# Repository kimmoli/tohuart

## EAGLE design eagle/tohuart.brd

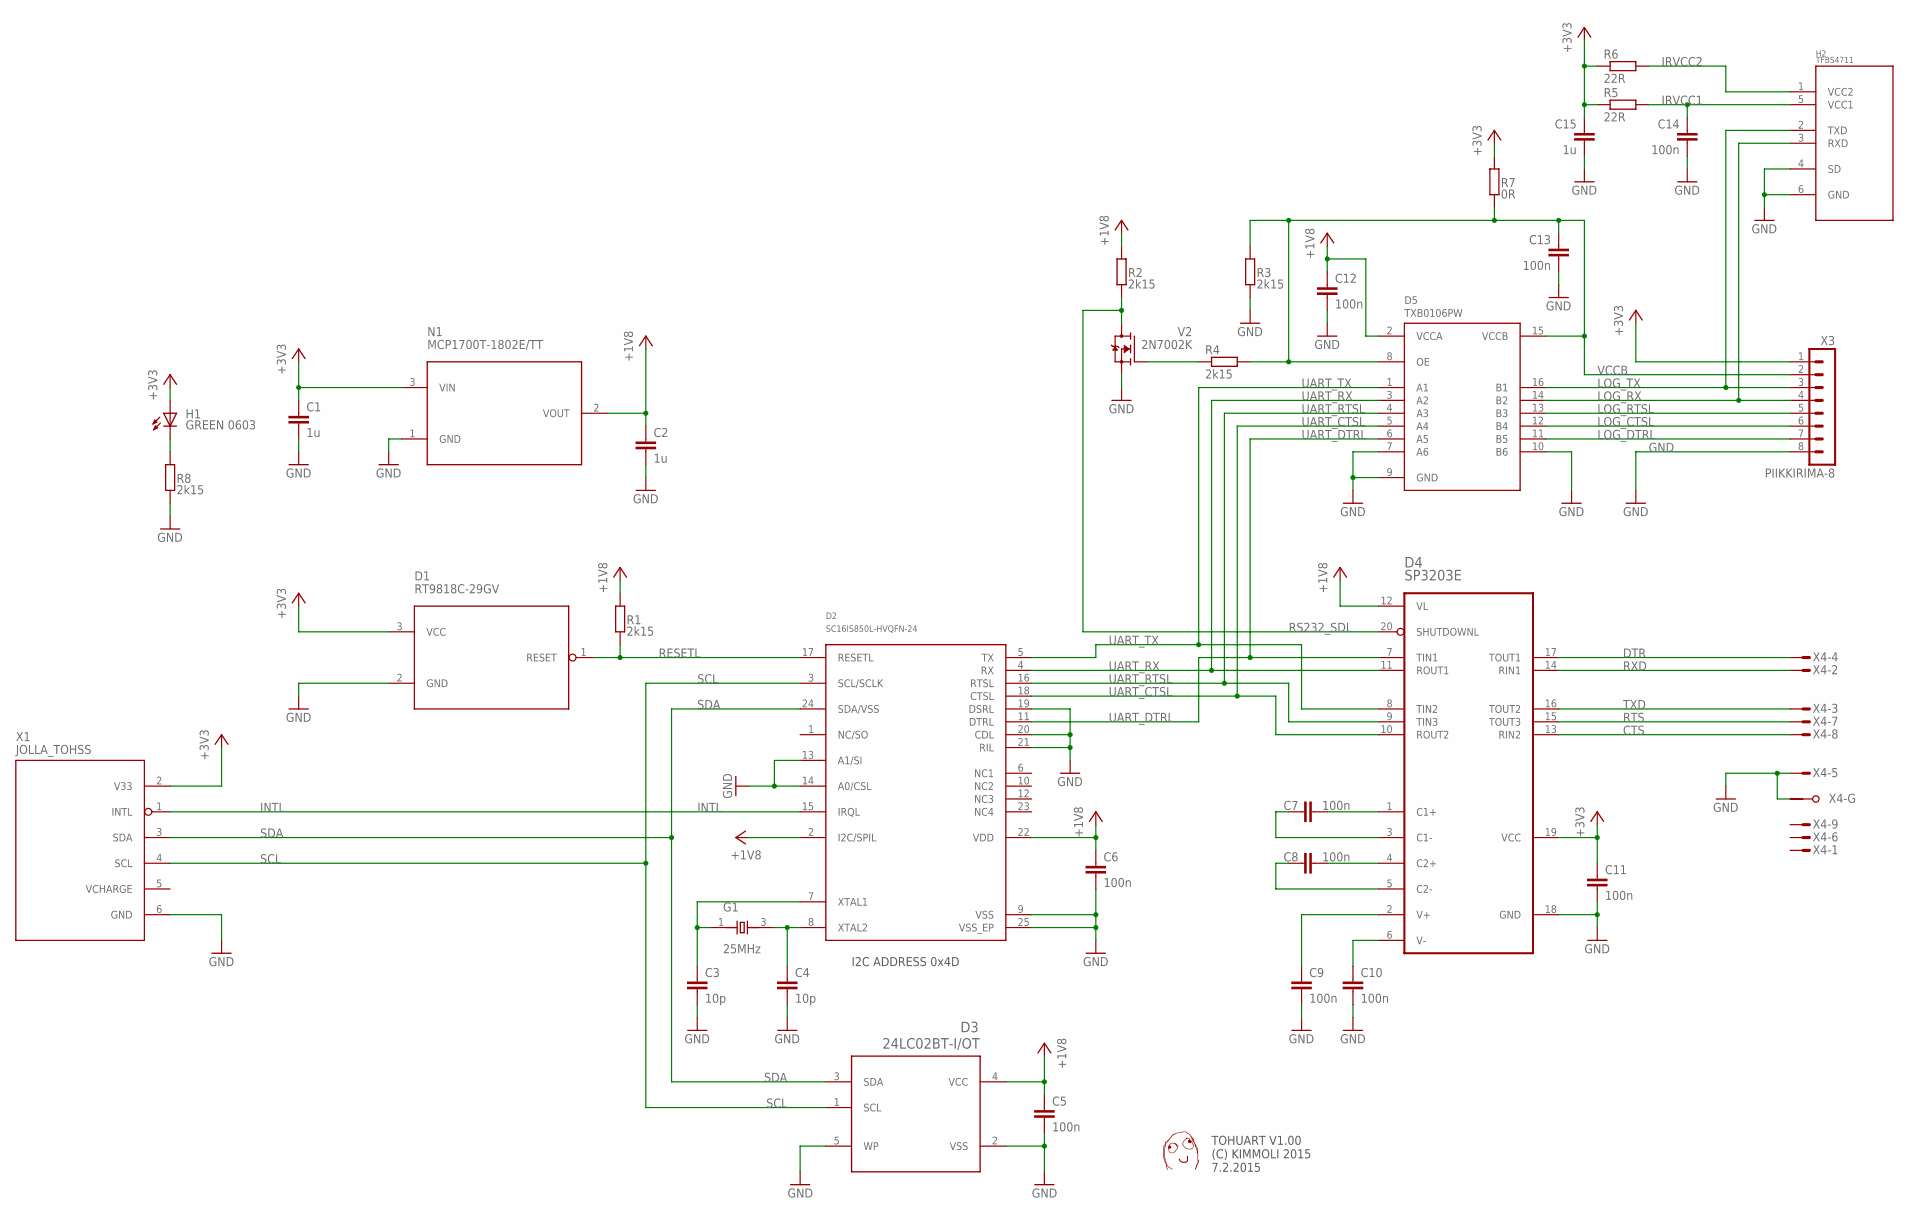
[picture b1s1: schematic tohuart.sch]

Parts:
C1, C2, C15: 1u; C0603
C3, C4: 10p; C0603
C5, C6, C7, C8, C9, C10, C11, C12, C13, C14: 100n; C0603
D1: RT9818C-29GV; SOT23
D2: SC16IS850L-HVQFN-24; HVQFN-24
D3: 24LC02BT-I/OT; SOT95P280X145-5N
D4: SP3203E; TSSOP-20
D5: TXB0106PW; TSSOP-16-065
G1: 25MHz; X_3225
H1: GREEN 0603; CHIP-LED0603
H2: TFBS4711
N1: MCP1700T-1802E/TT; SOT23
R1, R2, R3, R4, R8: 2k15; R0603
R5, R6: 22R; R0603
R7: 0R; R0603
U$1: DAFUG
V2: 2N7002K; SOT23
X1: JOLLA_TOHSS; JOLLA_TOH_POGOPADS
X3: PIIKKIRIMA-8
X4: M09VPS; M09VP

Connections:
+1V8: C2.1, C5.1, C6.1, C12.1, D2.2 (I2C/SPIL), D2.22 (VDD), D3.4 (VCC), D4.12 (VL), D5.2 (VCCA), N1.2 (VOUT), R1.2, R2.2
+3V3: C1.1, C11.1, C15.1, D1.3 (VCC), D4.19 (VCC), H1.A, N1.3 (VIN), R5.1, R6.1, R7.2, X1.2 (V33), X3.1
CTS: D4.13 (RIN2), X4.8 (M)
DTR: D4.17 (TOUT1), X4.4 (M)
GND: C1.2, C2.2, C3.2, C4.2, C5.2, C6.2, C9.2, C10.2, C11.2, C12.2, C13.2, C14.2, C15.2, D1.2 (GND), D2.9 (VSS), D2.13 (A1/SI), D2.14 (A0/CSL), D2.19 (DSRL), D2.20 (CDL), D2.21 (RIL), D2.25 (VSS_EP), D3.2 (VSS), D3.5 (WP), D4.18 (GND), D5.7 (A6), D5.9 (GND), D5.10 (B6), H2.4 (SD), H2.6 (GND), N1.1 (GND), R3.1, R8.1, V2.2 (S), X1.6 (GND), X3.8, X4.5 (M), X4.G1
INTL: D2.15 (IRQL), X1.1 (INTL)
IRVCC1: C14.1, H2.5 (VCC1), R5.2
IRVCC2: H2.1 (VCC2), R6.2
LOG_CTSL: D5.12 (B4), X3.6
LOG_DTRL: D5.11 (B5), X3.7
LOG_RTSL: D5.13 (B3), X3.5
LOG_RX: D5.14 (B2), H2.3 (RXD), X3.4
LOG_TX: D5.16 (B1), H2.2 (TXD), X3.3
unnamed: R4.1, V2.1 (G)
unnamed: H1.C, R8.2
unnamed: C10.1, D4.6 (V-)
unnamed: C9.1, D4.2 (V+)
unnamed: C8.1, D4.5 (C2-)
unnamed: C8.2, D4.4 (C2+)
unnamed: C7.1, D4.3 (C1-)
unnamed: C7.2, D4.1 (C1+)
unnamed: C4.1, D2.8 (XTAL2), G1.3 (X2)
unnamed: C3.1, D2.7 (XTAL1), G1.1 (X1)
RESETL: D1.1 (RESET), D2.17 (RESETL), R1.1
RS232_SDL: D4.20 (SHUTDOWNL), R2.1, V2.3 (D)
RTS: D4.15 (TOUT3), X4.7 (M)
RXD: D4.14 (RIN1), X4.2 (M)
SCL: D2.3 (SCL/SCLK), D3.1 (SCL), X1.4 (SCL)
SDA: D2.24 (SDA/VSS), D3.3 (SDA), X1.3 (SDA)
TXD: D4.16 (TOUT2), X4.3 (M)
UART_CTSL: D2.18 (CTSL), D4.10 (ROUT2), D5.5 (A4)
UART_DTRL: D2.11 (DTRL), D4.7 (TIN1), D5.6 (A5)
UART_RTSL: D2.16 (RTSL), D4.9 (TIN3), D5.4 (A3)
UART_RX: D2.4 (RX), D4.11 (ROUT1), D5.3 (A2)
UART_TX: D2.5 (TX), D4.8 (TIN2), D5.1 (A1)
VCCB: C13.1, D5.8 (OE), D5.15 (VCCB), R3.2, R4.2, R7.1, X3.2

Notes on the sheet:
I2C ADDRESS 0x4D
TOHUART V1.00 (C) KIMMOLI 2015 7.2.2015

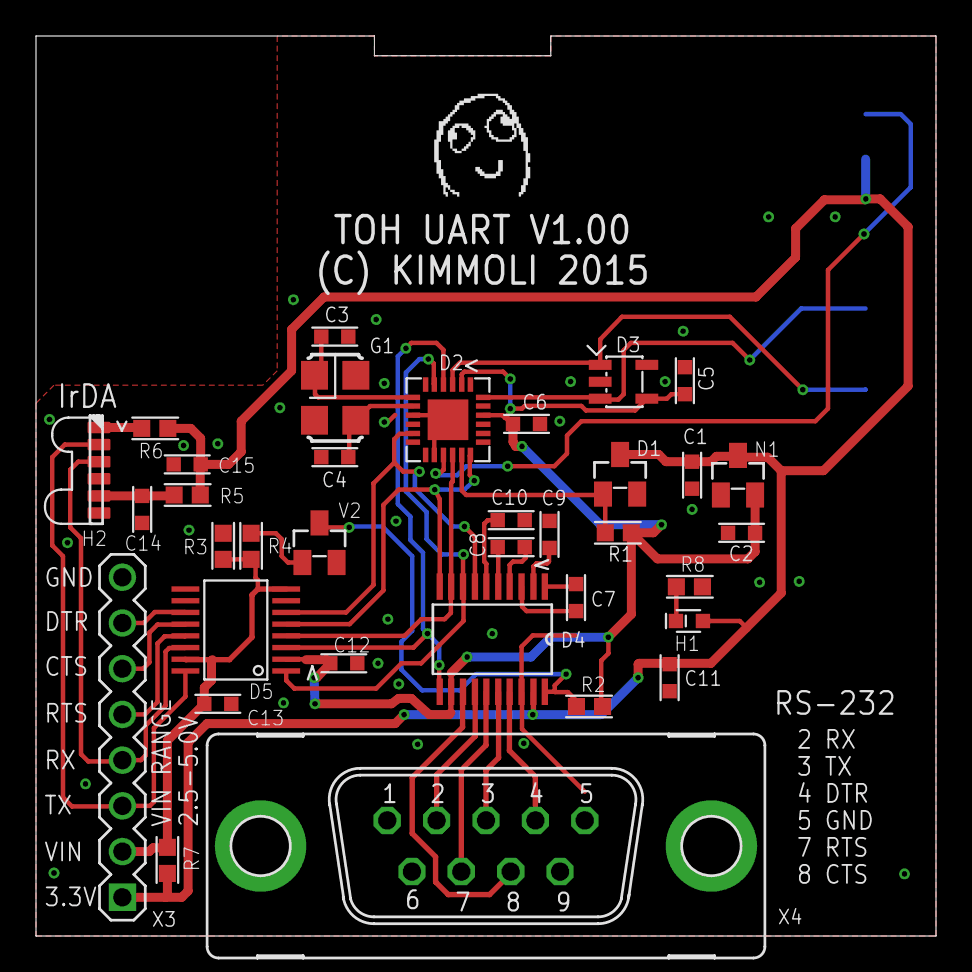
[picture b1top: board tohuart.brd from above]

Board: 2 copper layers, 50.0 x 50.0 mm, 37 parts (0 on the bottom side), 36 nets.

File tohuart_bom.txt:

Qty Value               Device              Package            Parts                                       Description                
1                       M09VPS              M09VP              X4                                          SUB-D                      
1   0R                  R-EU_R0603          R0603              R7                                          RESISTOR, European symbol  
10  100n                C-EUC0603           C0603              C5, C6, C7, C8, C9, C10, C11, C12, C13, C14 CAPACITOR, European symbol 
2   10p                 C-EUC0603           C0603              C3, C4                                      CAPACITOR, European symbol 
3   1u                  C-EUC0603           C0603              C1, C2, C15                                 CAPACITOR, European symbol 
2   22R                 R-EU_R0603          R0603              R5, R6                                      RESISTOR, European symbol  
1   24LC02BT-I/OT       24LC02BT-I/OT       SOT95P280X145-5N   D3                                          Serial EEPROM              
1   25MHz               XTAL_3225_SMD       X_3225             G1                                          CRYSTAL CLOCK OSCILLATORS  
1   2N7002K             2N7002K             SOT23              V2                                                                     
5   2k15                R-EU_R0603          R0603              R1, R2, R3, R4, R8                          RESISTOR, European symbol  
1   GREEN 0603          LEDCHIP-LED0603     CHIP-LED0603       H1                                          LED                        
1   MCP1700T-1802E/TT   MCP1700T-1802E/TT   SOT23              N1                                                                     
1   PIIKKIRIMA-8        PIIKKIRIMA-8        PIIKKIRIMA-8       X3                                                                     
1   RT9818C-29GV        RT9818C-29GV        SOT23              D1                                                                     
1   SC16IS850L-HVQFN-24 SC16IS850L-HVQFN-24 HVQFN-24           D2                                                                     
1   SP3203E             SP3203E             TSSOP-20           D4                                                                     
1   TFBS4711            TFBS4711            TFBS4711           H2                                                                     
1   TXB0106PW           TXB0106PW           TSSOP-16-065       D5

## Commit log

2015-07-03 upscale gerber pdf
